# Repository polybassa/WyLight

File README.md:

Wy_Light 
===========

 [Documentation](http://polybassa.github.com/WyLight/index.html)

Toolchain: 
----------
 [GNU Tools for ARM Embedded Processors](https://launchpad.net/gcc-arm-embedded/)	

Version:  
-----------
```(arm-none-eabi-gcc -v)```

gcc version 4.9.3 20141119 (release) `[ARM/embedded-4_9-branch revision 218278]` (GNU Tools for ARM Embedded Processors) 

Install:
-----------
```
./configure
make
```

Targets:
-----------
| Target	  | Description
|-----------------|--------------
| `test`          | build and execute unit tests        
| `firmware_esp`  | build ESP8266 firmware
| `firmware_pic`  | build PIC firmware                  
| `firmware_raspi`| build Raspberry Pi firmware
| `firmware_simu` | build PIC simulator                 
| `cli`           | build command line interface       
| `android_client`| build android ndk library

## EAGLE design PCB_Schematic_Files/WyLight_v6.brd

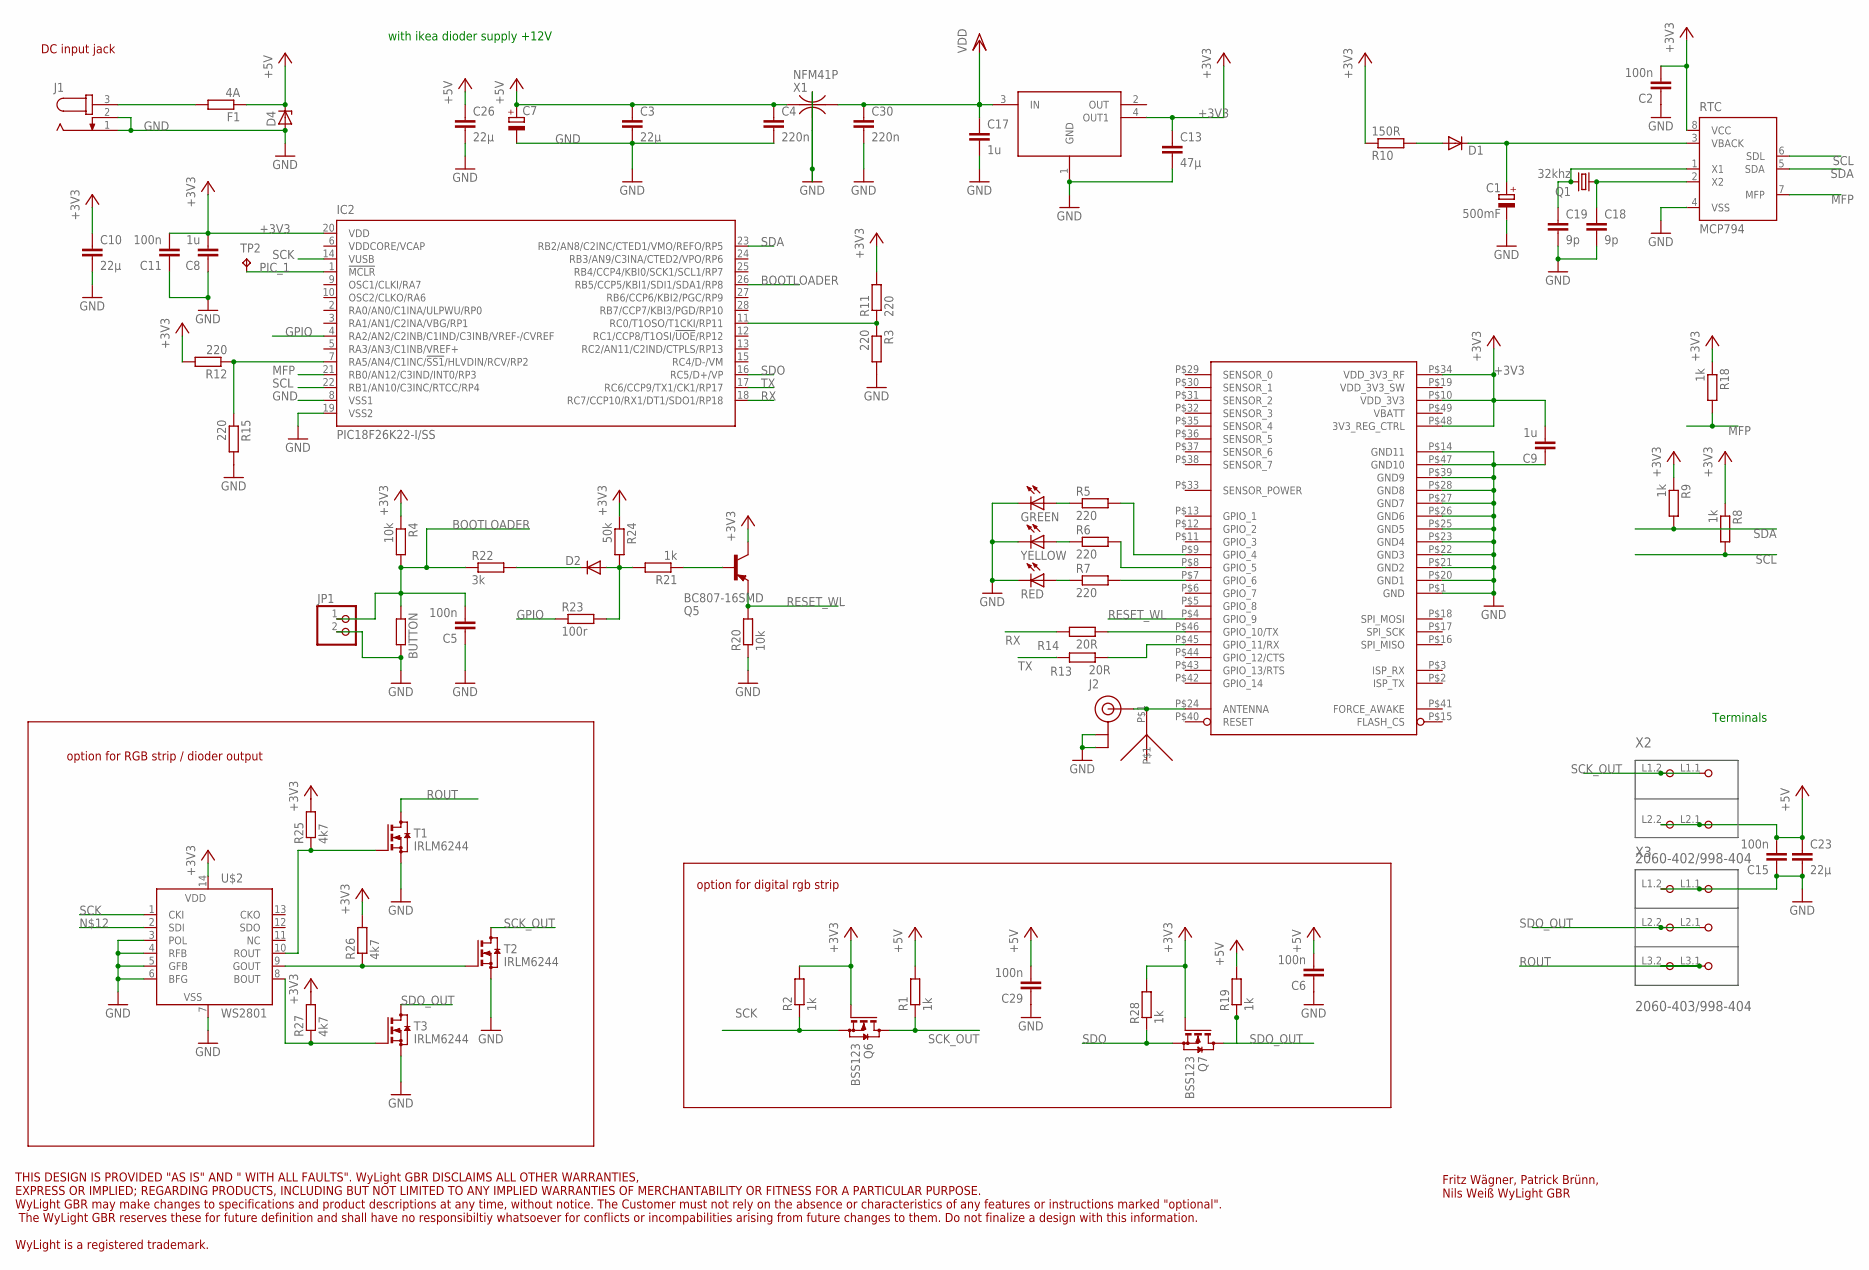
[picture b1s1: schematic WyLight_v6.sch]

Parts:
BUTTON: R-EU_M2309; M2309
C1: 500mF; E5-10,5
C2, C5, C6, C29: 100n; C0603K
C3, C10, C23, C26: 22µ; C1210
C4, C30: 220n; C0603
C7: CPOL-EUC/6032-28R; C/6032-28R
C8, C9, C17: 1u; C0603
C11, C15: 100n; C0603
C13: 47µ; C1210
C18, C19: 9p; C0603
D1, D2: DIODE-SOD323-W; SOD323-W
D4: ZENER-DIODESMB; SMB
F1: 4A; M2309
GREEN: LEDCHIPLED_0603; CHIPLED_0603
IC2: PIC18F26K22-I/SS; SSOP28
J1: JACK-PLUG0; SPC4077
J2: U.FL
JP1: PINHD-1X2_2.00; 1X02M
Q1: 32khz; Q_SMD_32_1,5
Q5: BC807-16SMD; SOT23-BEC
Q6, Q7: BSS123; SOT23
R1, R2, R8, R9, R18, R19, R21, R28: 1k; R0603
R3, R5, R6, R7, R11, R12, R15: 220; R0603
R4, R20: 10k; R0603
R10: 150R; R0603
R13, R14: 20R; R0603
R22: 3k; R0603
R23: 100r; R0603
R24: 50k; R0603
R25, R26, R27: 4k7; R0603
RED: LEDCHIPLED_0603; CHIPLED_0603
RTC: MCP794; SO-08
T1, T2, T3: IRLM6244; SOT23
TP2: TPB1,27; B1,27
U2: TLV1117; SOT223
U$1: RN171; WLAN_MOD_HAND
U$2: WS2801; SO14
U$3: WE-MCAWE-MCA; WE-MCA
X1: NFM41P
X2: 2060-402/998-404; P-2060-402/998-404
X3: 2060-403/998-404; P-2060-403/998-404
YELLOW: LEDCHIPLED_0603; CHIPLED_0603

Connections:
+3V3: C2.2, C8.2, C9.2, C10.1, C11.2, C13.1, IC2.20 (VDD), Q5.C, Q6.1 (G), Q7.1 (G), R2.2, R4.1, R8.1, R9.1, R10.1, R11.2, R12.2, R18.1, R24.1, R25.2, R26.2, R27.2, R28.2, RTC.8 (VCC), U2.4 (OUT1), U$1.P$10 (VDD_3V3), U$1.P$34 (VDD_3V3_RF), U$1.P$48 (3V3_REG_CTRL), U$2.14 (VCC)
+5V: C3.1, C4.1, C6.2, C7.+, C15.2, C23.1, C26.1, C29.2, D4.C, F1.1, R1.2, R19.2, X1.1, X2.L2.1 (P2.1), X2.L2.2 (P2.2)
BOOTLOADER: BUTTON.1, C5.2, IC2.26 (RB5/CCP5/KBI1/SDI1/SDA1/RP8), JP1.1, R4.2, R22.1
GND: BUTTON.2, C1.-, C2.1, C3.2, C4.2, C5.1, C6.1, C7.-, C8.1, C9.1, C10.2, C11.1, C13.2, C15.1, C17.2, C18.2, C19.2, C23.2, C26.2, C29.1, C30.2, D4.A, GREEN.C, IC2.8 (VSS1), IC2.19 (VSS2), J1.1, J1.2, J2.P$1 (GND), J2.P$2 (GND), JP1.2, R3.2, R15.2, R20.1, RED.C, RTC.4 (VSS), T1.2 (S), T2.2 (S), T3.2 (S), U2.1 (GND), U$1.P$1 (GND), U$1.P$14 (GND11), U$1.P$20 (GND1), U$1.P$21 (GND2), U$1.P$22 (GND3), U$1.P$23 (GND4), U$1.P$25 (GND5), U$1.P$26 (GND6), U$1.P$27 (GND7), U$1.P$28 (GND8), U$1.P$39 (GND9), U$1.P$47 (GND10), U$2.3 (POL), U$2.4 (RFB), U$2.5 (GFB), U$2.6 (BFG), U$2.7 (GND), X1.2@1 (2), X1.2@2 (2), X3.L1.1 (P1.1), X3.L1.2 (P1.2), YELLOW.C
GPIO: IC2.4 (RA2/AN2/C2INB/C1IND/C3INB/VREF-/CVREF), R23.1
MFP: IC2.21 (RB0/AN12/C3IND/INT0/RP3), R18.2, RTC.7 (MFP)
unnamed: F1.2, J1.3
unnamed: J2.P$3 (SIGNAL), U$1.P$24 (ANTENNA), U$3.P$1
unnamed: GREEN.A, R5.1
unnamed: R14.2, U$1.P$46 (GPIO_10/TX)
unnamed: R6.1, YELLOW.A
unnamed: R7.1, RED.A
unnamed: R7.2, U$1.P$7 (GPIO_6)
unnamed: R6.2, U$1.P$8 (GPIO_5)
unnamed: R5.2, U$1.P$9 (GPIO_4)
unnamed: C1.+, D1.C, RTC.3 (VBACK)
unnamed: R13.2, U$1.P$45 (GPIO_11/RX)
unnamed: D1.A, R10.2
unnamed: C19.1, Q1.2, RTC.1 (X1)
unnamed: IC2.7 (RA5/AN4/C1INC/!SS1!/HLVDIN/RCV/RP2), R12.1, R15.1
unnamed: IC2.11 (RC0/T1OSO/T1CKI/RP11), R3.1, R11.1
unnamed: C18.1, Q1.1, RTC.2 (X2)
unnamed: D2.C, R22.2
unnamed: R25.1, T1.1 (G), U$2.10 (ROUT)
unnamed: R26.1, T2.1 (G), U$2.9 (GOUT)
unnamed: R27.1, T3.1 (G), U$2.8 (BOUT)
unnamed: Q5.B, R21.1
unnamed: D2.A, R21.2, R23.2, R24.2
PIC_1: IC2.1 (!MCLR), TP2.TP
RESET_WL: Q5.E, R20.2, U$1.P$4 (GPIO_9)
ROUT: T1.3 (D), X3.L3.1 (P3.1), X3.L3.2 (P3.2)
RX: IC2.18 (RC7/CCP10/RX1/DT1/SDO1/RP18), R14.1
SCK: IC2.14 (VUSB), Q6.2 (S), R2.1, U$2.1 (CKI)
SCK_OUT: Q6.3 (D), R1.1, T2.3 (D), X2.L1.1 (P1.1), X2.L1.2 (P1.2)
SCL: IC2.22 (RB1/AN10/C3INC/RTCC/RP4), R8.2, RTC.6 (SDL)
SDA: IC2.23 (RB2/AN8/C2INC/CTED1/VMO/REFO/RP5), R9.2, RTC.5 (SDA)
SDO: IC2.16 (RC5/D+/VP), Q7.2 (S), R28.1
SDO_OUT: Q7.3 (D), R19.1, T3.3 (D), X3.L2.1 (P2.1), X3.L2.2 (P2.2)
TX: IC2.17 (RC6/CCP9/TX1/CK1/RP17), R13.1
VDD: C17.1, C30.1, U2.3 (IN), X1.3

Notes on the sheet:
with ikea dioder supply +12V
Terminals
option for RGB strip / dioder output
option for digital rgb strip
DC input jack
Fritz Wägner, Patrick Brünn, Nils Weiß WyLight GBR
THIS DESIGN IS PROVIDED "AS IS" AND " WITH ALL FAULTS". WyLight GBR DISCLAIMS ALL OTHER WARRANTIES, EXPRESS OR IMPLIED; REGARDING PRODUCTS, INCLUDING BUT NOT LIMITED TO ANY IMPLIED WARRANTIES OF MERCHANTABILITY OR FITNESS FOR A PARTICULAR PURPOSE. WyLight GBR may make changes to specifications and 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

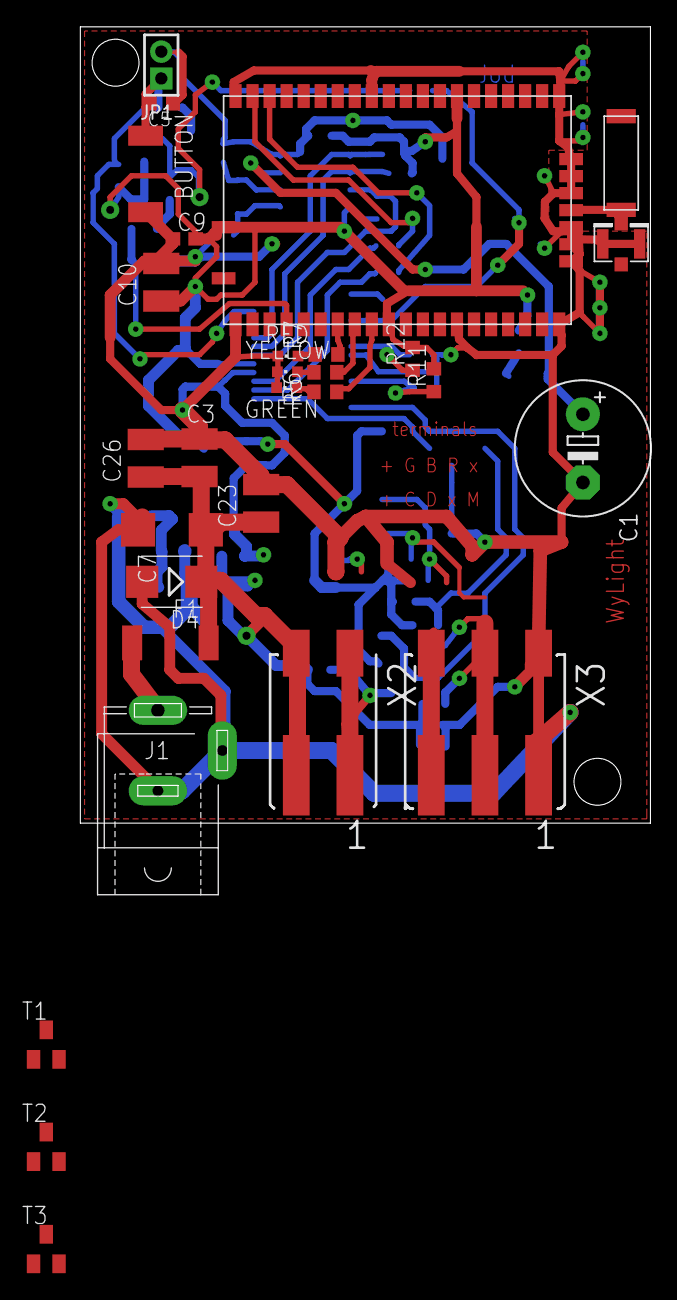
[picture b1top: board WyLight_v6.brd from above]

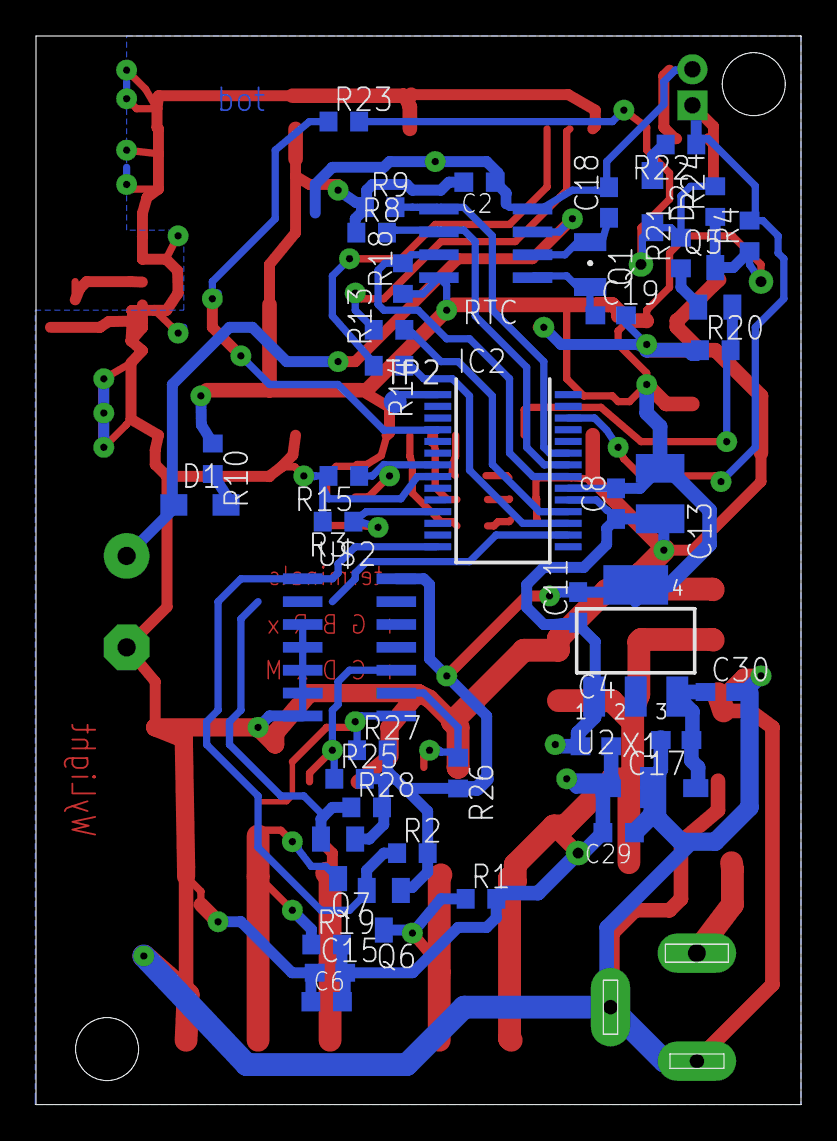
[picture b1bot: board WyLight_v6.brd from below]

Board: 2 copper layers, 42.5 x 59.4 mm, 74 parts (45 on the bottom side), 40 nets.

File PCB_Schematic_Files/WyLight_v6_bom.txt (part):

WyLight BOM:

Part   Value            Device            Package            Description                                                                                                                                                                                                                                                                                                                                                                                                                                                                                                                                                                                                                                                                                                                                                                 MF MPN OC_FARNELL OC_NEWARK PROD_ID    TP_SIGNAL_NAME VALUE
BUTTON                  pushbutton	  M2309              SMD                                                                                                                                                                                                                                                                                                                                                                                                                                                                                                                                                                                                                                                                                                                                                                                                              
C1     500mF            CPOL-EUE5-10.5    E5-10,5            POLARIZED CAPACITOR, European symbol                                                                                                                                                                                                                                                                                                                                                                                                                                                                                                                                                                                                                                                                                                                                                                                                   
C2     100n             C-EUC0603K        C0603K             CAPACITOR, European symbol                                                                                                                                                                                                                                                                                                                                                                                                                                                                                                                                                                                                                                                                                                                                                                                                             
C3     22µ              C-EUC1210         C1210              CAPACITOR, European symbol                                                                                                                                                                                                                                                                                                                                                                                                                                                                                                                                                                                                                                                                                                                                                                                                             
C4     220n             C-EUC0603         C0603              CAPACITOR, European symbol                                                                                                                                                                                                                                                                                                                                                                                                                                                                                                                                                                                                                                                                                                                                                                                                             
C5     100n             C-EUC0603K        C0603K             CAPACITOR, European symbol                                                                                                                                                                                                                                                                                                                                                                                                                                                                                                                                                                                                                                                                                                                                                                                                             
C6     100n             C-EUC0603K        C0603K             CAPACITOR, European symbol                                                                                                                                                                                                                                                                                                                                                                                                                                                                                                                                                                                                                                                                                                                                                                                                             
C7     22u              CPOL-EUC/6032-28R C/6032-28R         POLARIZED CAPACITOR, European symbol                                                                                                                                                                                                                                                                                                                                                                                                                                                                                                                                                                                                                                                                                                                                                                                                   
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
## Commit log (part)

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2014-12-15 fix linker script for bootloader
2014-12-15 small fixes
2014-12-22 cleanup global defines for bootloader
2014-12-22 Validate returnvalue of Bootloader
2014-12-31 migrate android app from Eclipse to Android Studio 1.0
2014-12-31 fix android build
2015-01-05 Android: add copyright notice to NoSwipeViewPager.java
2015-01-09 add cppcheck to build
2015-01-10 change print macro to avoid compiler warnings
2015-01-10 fix cppcheck errors
2015-01-11 add unit test for WyFirmwareDownloader
2015-01-11 more test data
2015-01-11 check for existing sha files now
2015-01-11 add WyFirmwareDownloader unit test to makefile
2015-01-11 add WyLight FileLoader Command Line Interface to project
2015-01-11 documentation
2015-01-12 android: released 0.38 to app store -> increment version counter
2015-01-18 test new linker file
2015-01-18 test new linker script
2015-01-19 Revert "test new linker script"
    This reverts commit d963216ccef2125faf186f2c5d8a7d379dd48837.
2015-01-19 fix cli build with refactored ConfigControl
2015-01-24 Fix Makefiles
2015-01-25 some small changes
2015-01-25 add build wrapper for Xcode
2015-01-25 finish BroadcastReceiver separation
2015-01-25 clean headers, includes and traces
2015-01-25 fix simulator build
2015-01-25 fix broken BroadcastReceiver_ut build
2015-01-25 add android_client to README.md targets
2015-01-25 fix configure script
2015-01-25 finally fixed cppcheck
2015-01-26 fix cc_fw on nils osx
2015-01-28 fix broadcast receiver bug
2015-02-03 cleanup makedefs and fix unit test
2015-02-03 add BriadcastMessage.cpp to android makefile
2015-02-04 changed linker from ld to gcc
2015-02-04 simplify BroadcastReceiver
2015-02-04 remove unused function BroadcastReceiver::DeleteRecentEndpointFile()
2015-02-05 allow compiler to use copy elision
2015-02-05 refactor Endpoint serialization
2015-02-06 change trace
2015-02-06 reverse iOS trace
2015-02-06 add delete recent endpoint file
2015-02-06 refactor BroadcastReceiver::operator()
2015-02-06 undo changes in android makefile
2015-02-07 cleanup CommandIO trace
2015-02-07 removed WY_DEBUG and fix DEBUG in driverlib
2015-02-07 clean up some defines and remove some UART_PRINTs
2015-02-07 add BroadcastReceiver::NOP() function as dummy implementation for the onNewRemote callback -> this will simplify all if(mNewRemote) mNewRemote(x, y) calls to mNewRemote(x,y) which omit the danger of 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
    remove hacky make target "library_fast_test"
2015-02-08 clean up Makefiles
2015-02-08 fix sim build
2015-02-09 simplify folder structure and make files
2015-02-09 change configure script
2015-02-09 change to compiler gcc version 4.9.3 20141119 (release) [ARM/embedded-4_9-branch revision 218278]
2015-02-12 add wercker file
2015-02-19 start reimplementing Network Driver
2015-02-19 change environment to build simpleLink library with c++
2015-02-19 get simple link driver working
2015-02-19 work in progress
2015-02-21 changed sl_trace filename to avoid conflicts
2015-02-21 Uncrustify configuration changes
2015-02-21 cleanup driverlib
2015-02-23 add pre-commit hook
2015-02-23 change pre-commit hook
2015-02-23 disable pre-commit uncrustify hook on Master
2015-02-23 rename target codeformatter to uncrustify
2015-02-24 small cleanups
2015-02-24 change uncrustify config
2015-02-24 disable pre-commit hook until checked on osx, too
2015-02-24 Get precommit hook running on OS X
2015-02-24 add script to download, build and install uncrustify
2015-02-24 CAUTION: All source files are formatted with WyLight formatting rules, now.
2015-02-25 change comma settings in uncrustify config
2015-02-25 changed uncrustify rules from add to force
2015-02-25 add script to prepare nightly and remote builds
2015-02-27 formatting
2015-03-07 add status mails for autobuild
2015-03-07 fix send mail commands with bash
2015-03-07 fix sendmail for cronjob
2015-03-07 fix build for fresh repositories
2015-03-14 fix minor bug
2015-03-14 refactoring of Timer class
2015-03-14 Timer and Pwm refactoring
2015-03-15 Add ADC driver
2015-03-16 First sketch of I2C class
2015-03-16 Add LockGuard class and implemented I2C driver
2015-03-19 Codeformatting
2015-03-25 fix bug in PwmTaskHandle
2015-03-30 Improve debug trace in driverlib and uncrustify driverlib
2015-03-30 bugfix in simpleLinkDriver
2015-03-30 change .gitignore
2015-03-30 add eclipse project files
2015-03-30 fix bootloader build
2015-04-01 Update Makefile.firmware
    fix unit test build
2015-04-02 small improvements on build script
2015-04-02 fix bug in Makefile
2015-04-02 WyFiledownloader_ut isn't running on edison and raspi, disable unittest for now
2015-04-04 fix bug in autobuild.sh
2015-04-04 #220 add firmware version number in CC3200
2015-04-06 remove macro
2015-04-06 Create BootloaderControl object to seperate duties in WiflyControl
2015-04-06 Fix Android Library Build
2015-04-07 Remove WiflyControlNoThrow Class
2015-04-07 add endpoint type field to ObjC wrapper
2015-04-07 code cleaning
2015-04-11 restore lost google_play stuf
2015-04-11 cleanup makefiles
2015-04-12 simplify token extractor function
2015-04-13 move extract firmware version methode from control to firmwarecontrol
2015-04-13 add startupmanager implementation for CC3200 and RN171
2015-04-14 add result message
2015-04-14 fix bug in log function
2015-04-16 cleanup main file
2015-04-18 uncrustify
2015-04-19 move cc3200 platform
2015-04-20 add built in self test
2015-04-20 improved bugfix of build server build
2015-04-28 update iCarousel library
2015-04-28 Fix broken wylight ios App
2015-05-11 remove sim target if openssl is not available
2015-05-25 fix simulator broadcast target
2015-07-08 add ambilight proof of concept with boblight
2015-07-13 refactor control creation into static Control::Create()
2015-07-13 rename boblight_client to boblight
2015-07-13 refactor endpoint creation; use new constructor which takes a cstring as ip address
2015-07-13 add missing Endpoint.cpp to android makefile
2016-03-07 enable Travis CI
2016-03-07 update travis file
2016-03-07 change for travis
2016-03-08 fix for travis build
2016-03-08 add cc8e travis build
2016-03-10 firmware: cleanup
    - refactor Eeprom_Init()
    - refactor isr in x86_wrapper
2016-03-10 firmware: refactor opengl simulation
    - rename x86_gl.c to spi_opengl.c
    - move SPI_*() functions from x86_wrapper to spi_opengl
2016-03-10 firmware: remove x86_wrapper.h
    - fix some unused variables and defines in firmware builds
2016-03-10 firmware: split eeprom in pic and fake (RAM) implementation
2016-03-10 README: add 'firmware_raspi' target
2016-03-10 autoconf: add check for 'ftp'
    'ftp' is required by unittest FtpServer_ut
2016-03-11 firmware raspi/simu: fix broadcast address
2016-03-11 firmware: fix CommandIo unittest
    Timer_PrintCycleTime() is used only by PIC firmware and defined as 0 with commit 50cee162c6b60d39e3ee1545417c7e08760ede4e. We undo this change and add a dummy (memcpy() implementation for CommandIO_u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
2016-05-01 linkit: add ttyS as SPI sink
    On LinkIt 7688 Duo WyLight firmware runs on the OpenWRT mips MPU, which
    is connected to an ATmega32U4 MCU. MPU<->MCU are connected by a serial
    line.
    SPI and PWM of the MCU are used for output. spi_ttyS.c is the driver
    running on MPU sending the LEDStrip states as byte array over serial to
    the MCU.
2016-05-01 linkit: send full 32 led buffer
    always transfer 96 bytes, but limit the amount of cycles on the MPU side
2016-05-01 linkit: cleanup + simplify go4LED() signature
2016-05-04 linkit: correct license header
2016-09-10 linkit: run uncrustify
    add linkit firmware files to uncrustify filelist
2016-09-20 linkit: add linkit 7688 openwrt sdk dependency
    To build firmware_linkit the OpenWrt-SDK-ramips-mt7688 is required.
2016-10-04 linkit: fix pwm init -> force pinmuxing
    setup pinmuxing on SPI_Init() for linkit firmware
2016-10-16 eeprom_file: add eeprom as file implementation
    For devices with a filesystem such as simulator, raspberrypi or linkit
    we implement a fake eeprom as file
2016-10-18 eeprom_file: add eeprom unittest and fix overflow bug
2016-11-01 firmware: add target firmware_sdcc
    - add firmware_sdcc to Makefile
    - begin porting of pic firmware to sdcc
2016-11-01 firmware: port eeprom and flash driver to sdcc
2016-11-03 firmware: sdcc: c code compiles, but assembler and linker throw errors
2016-11-03 firmware: sdcc: remove eeprom_pic.c
2016-11-04 firmware: sdcc: port timer.c
2016-11-04 firmware: sdcc: port rtc.c
2016-11-07 android: upgrade to ndk-r12b and android studio 2.2.2
2016-11-08 firmware: refactor iic.c (only search & replace)
2016-11-08 firmware: remove unused I2C_Read/WriteBlock()
2016-11-08 cc3200: begin complete removal of cc3200
    cc3200 became to expensive and has no advantages over linkit7688.
    As the CC3200 port is to complex, we decided to remove cc3200 support
    completely. However the branch obsolete-cc3200 should remain, to keep
    easy access to the cc3200 implementation, if it might become of
    interest again.
    This commit starts the removal by simple deleting cc3200 only files.
2016-11-08 firmware: remove cc3200 #ifdefs
2016-11-09 docu: try to fix makefile
2016-11-10 update configure script with autoconf
2016-11-14 firmware: prepare partial ledbuffer update
2016-12-09 cmd: add 'setmove' command
    implementaion of 'running light'
2017-02-03 script: unittest gradient/move command
    - test gradient and move command in ScriptCtrl_ut
    - refactor FwCmd*::TOKEN into Script.cpp
    - fix SPI_SendLedBuffer(uint8_t* buf, uns8 length) for all platforms
2017-02-04 cli: fix formatting in help text
2017-02-04 firmware: increase version number
2017-02-04 android: upgrade android studio and app
2017-04-28 x86: remove dead nogl code
2017-04-28 x86: replace ifdef'd usleep(10) with Platform_MainLoopSleep
2017-04-28 update copyright notice for changed files
2017-05-26 firmware: remove dead code from isr
2017-05-27 firmware: main: merge __CC8E__ specific block
2017-05-27 firmware: move platform specific g_ResetEnvironment into Platform_Main macro
2017-05-27 firmware: move do_and_measure macro into timer.h
2017-05-27 firmware: move pic specific isr into isr_pic.c
2017-05-28 firmware: remove obsolete comment
2017-05-28 esp8266: udp broadcast hello world
2017-05-28 esp8266: proof of concept OTA update
2017-05-31 esp8266: proof of concept use of esp-open-sdk
    download and build the esp-open-sdk (gcc cross-compiler toolchain) with:
    './tools/install_esp_toolchain.sh'
    build an example firmware (from esp-open-sdk) with:
    'cd esp8266 && make'
    to flash it connect sparkfun usb thing dev to /dev/ttyUSB0 and run:
    'make flash'
2017-06-03 firmware: split platform.h into pic and linux version
2017-06-03 firmware: sync platform_linux/pic.h
2017-06-04 firmware: split main into pic and common
2017-06-04 esp: connects to hardcoded SSID/PASS and sends broadcasts
2017-06-08 firmware: remove obsolete code from usart.c
    remove it now, since it pollutes git grep output
2017-06-08 esp: working better now
2017-06-09 part1: reuse usart_socket for simu/linkit/raspi
2017-06-09 sp: make merged usart_socket build for esp
2017-06-09 firmware: reuse timer_thread.c for all non CC8E targets
2017-06-09 firmware: remove unused timer macros
2017-06-10 firmware: make x86_wrapper obsolete by multiplatform rtc_linux.c
2017-06-11 ci: add gperf for esp build
2017-06-11 ci: add makeinfo for esp build
2017-06-11 ci: move esp toolchain from before_install to install
2017-06-13 firmware: harmonize platform_esp/linux.h
2017-06-28 .travis: add autoconf, bison and flex to build esp toolchain
2017-06-28 .travis: use CT_ALLOW_BUILD_AS_ROOT_SURE=y for esp toolchain build
2017-06-28 fix ISO C does not support '__FUNCTION__' predefined identifier
2017-06-28 library/cli: fix broken -lpthread support
2017-06-28 travis: add make firmware_esp
2017-06-28 Makefile: reorder LDFLAGS for *.bin targets
2017-06-30 travis: fix 'ImportError: No module named serial'
2017-07-01 firmware: use same compiler flags for raspi, linkit and simu
2017-07-02 firmware: refactor usart_socket.c for simu/linkit/raspi
2017-07-02 firmware: transform x86_wrapper into rtc_linux
2017-07-02 esp: add ota tftp server

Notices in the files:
parts and their libraries:
SparkFun-Connectors: Licensing: Creative Commons ShareAlike 4.0 International - https://creativecommons.org/licenses/by-sa/4.0
